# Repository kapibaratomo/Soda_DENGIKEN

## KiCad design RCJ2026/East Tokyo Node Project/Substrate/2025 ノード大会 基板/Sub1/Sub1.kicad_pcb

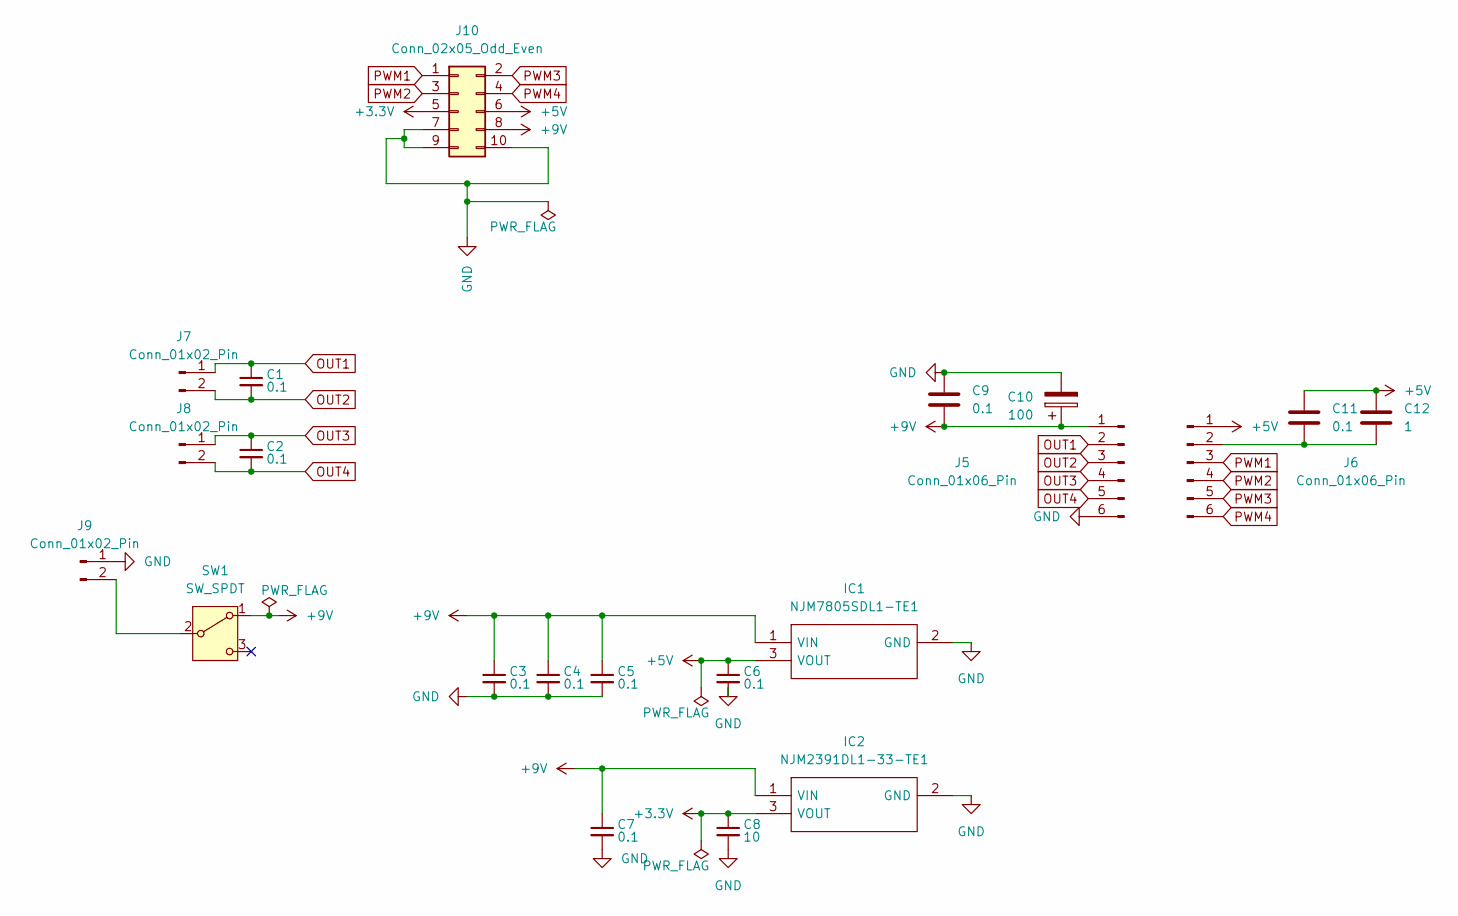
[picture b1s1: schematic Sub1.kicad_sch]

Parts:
C1, C2, C3, C4, C5, C6, C7, C9, C11: 0.1; C_0402_1005Metric
C8: 10; C_0603_1608Metric
C10: 100; C_Radial_D6.3mm_H7.0mm_P2.50mm
C12: 1; C_0402_1005Metric
IC1: NJM7805SDL1-TE1; NJM7805SDL1TE1
IC2: NJM2391DL1-33-TE1; NJM2391DL133TE1
J5, J6: Conn_01x06_Pin; PinSocket_1x06_P2.54mm_Vertical
J7, J8, J9: Conn_01x02_Pin; JST_XH_B2B-XH-A_1x02_P2.50mm_Vertical
J10: Conn_02x05_Odd_Even; IDC-Header_2x05_P2.54mm_Vertical
SW1: SW_SPDT; 2MS3T1B4M2QES

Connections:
+3.3V: C8.1, IC2.3 (VOUT), J10.5
+5V: C6.1, C11.1, C12.1, IC1.3 (VOUT), J6.1, J10.6
+9V: C3.1, C4.1, C5.1, C7.1, C9.2, C10.1, IC1.1 (VIN), IC2.1 (VIN), J5.1, J10.8, SW1.1 (A)
GND: C3.2, C4.2, C5.2, C6.2, C7.2, C8.2, C9.1, C10.2, IC1.2 (GND), IC2.2 (GND), J5.6, J9.1, J10.7, J10.9, J10.10
unnamed: C11.2, C12.2, J6.2
unnamed: J9.2, SW1.2 (B)
OUT1: C1.1, J5.2, J7.1
OUT2: C1.2, J5.3, J7.2
OUT3: C2.1, J5.4, J8.1
OUT4: C2.2, J5.5, J8.2
PWM1: J6.3, J10.1
PWM2: J6.4, J10.3
PWM3: J6.5, J10.2
PWM4: J6.6, J10.4

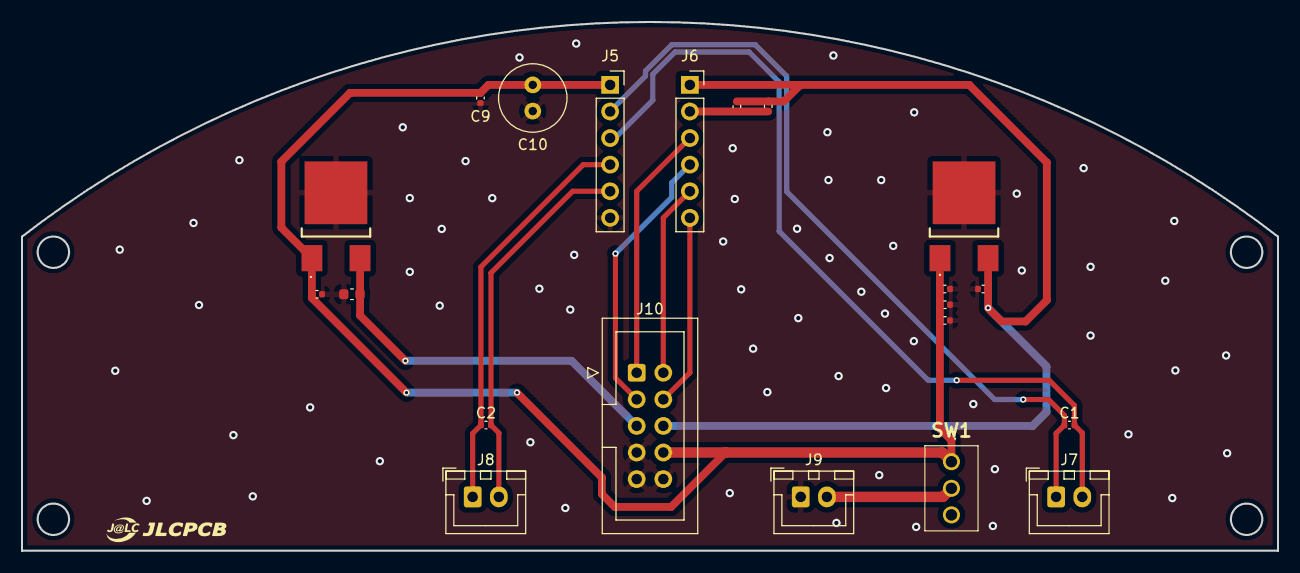
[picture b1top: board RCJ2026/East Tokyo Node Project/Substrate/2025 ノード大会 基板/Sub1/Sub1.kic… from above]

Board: 2 copper layers, 120.0 x 50.5 mm, 21 parts (0 on the bottom side), 14 nets.

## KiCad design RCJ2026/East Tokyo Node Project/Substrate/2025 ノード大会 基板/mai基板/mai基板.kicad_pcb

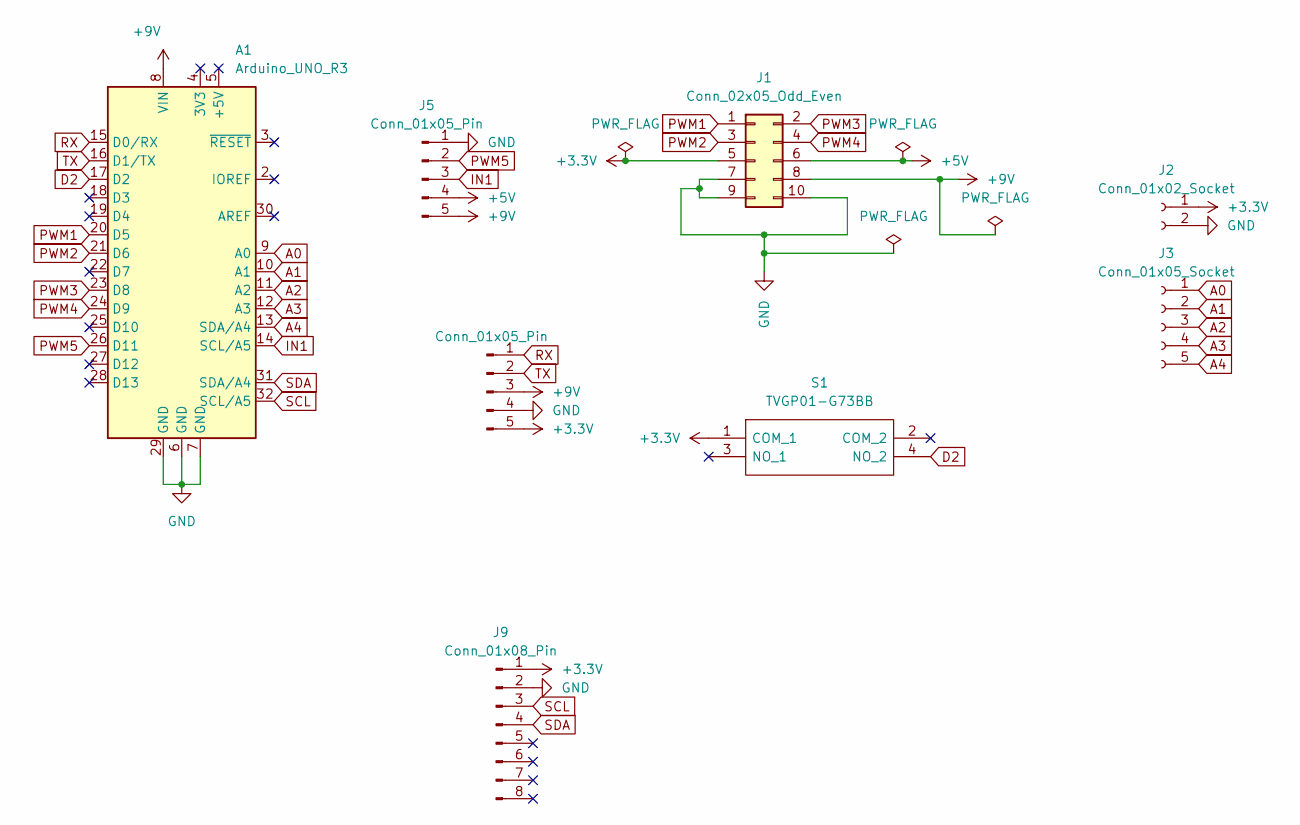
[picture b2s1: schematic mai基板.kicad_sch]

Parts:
A1: Arduino_UNO_R3
J1: Conn_02x05_Odd_Even; IDC-Header_2x05_P2.54mm_Vertical
J2: Conn_01x02_Socket; JST_XH_B2B-XH-A_1x02_P2.50mm_Vertical
J3: Conn_01x05_Socket; JST_XH_B5B-XH-A_1x05_P2.50mm_Vertical
J4, J5: Conn_01x05_Pin; JST_XH_B5B-XH-A_1x05_P2.50mm_Vertical
J9: Conn_01x08_Pin; PinSocket_1x08_P2.54mm_Vertical
S1: TVGP01-G73BB; TVGP01G73BB; Manufacturer_Part_Number TVGP01-G73BB

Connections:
+3.3V: J1.5, J2.1, J4.5, J9.1, S1.1 (COM_1)
+5V: J1.6, J5.4
+9V: A1.8 (VIN), J1.8, J4.3, J5.5
A0: A1.9 (A0), J3.1
A1: A1.10 (A1), J3.2
A2: A1.11 (A2), J3.3
A3: A1.12 (A3), J3.4
A4: A1.13 (SDA/A4), J3.5
D2: A1.17 (D2), S1.4 (NO_2)
GND: A1.6 (GND), A1.7 (GND), A1.29 (GND), J1.7, J1.9, J1.10, J2.2, J4.4, J5.1, J9.2
IN1: A1.14 (SCL/A5), J5.3
PWM1: A1.20 (D5), J1.1
PWM2: A1.21 (D6), J1.3
PWM3: A1.23 (D8), J1.2
PWM4: A1.24 (D9), J1.4
PWM5: A1.26 (D11), J5.2
RX: A1.15 (D0/RX), J4.1
SCL: A1.32 (SCL/A5), J9.3
SDA: A1.31 (SDA/A4), J9.4
TX: A1.16 (D1/TX), J4.2

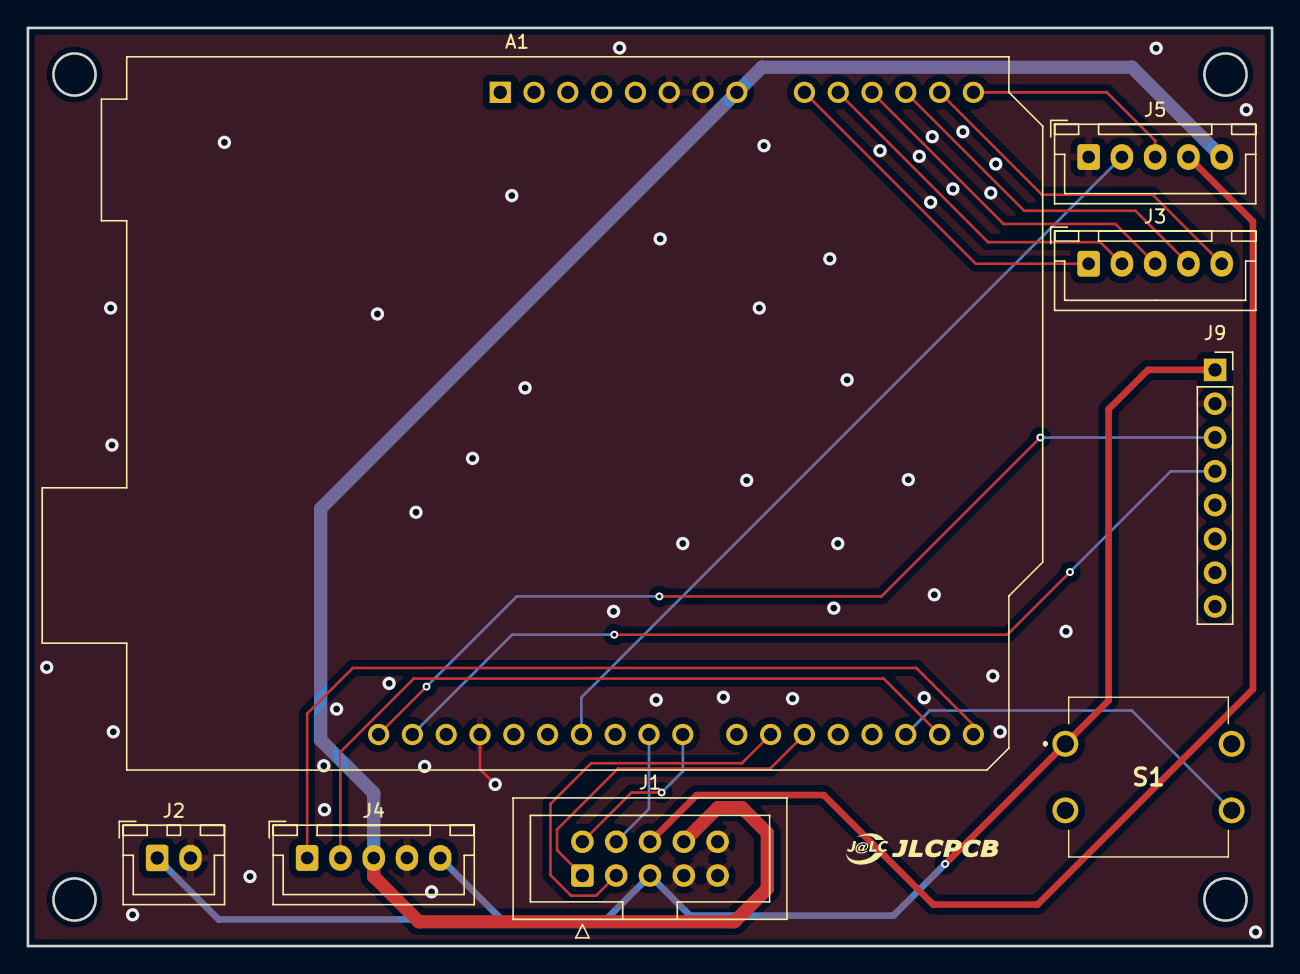
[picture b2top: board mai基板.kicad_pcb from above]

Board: 2 copper layers, 93.5 x 69.0 mm, 8 parts (0 on the bottom side), 20 nets.

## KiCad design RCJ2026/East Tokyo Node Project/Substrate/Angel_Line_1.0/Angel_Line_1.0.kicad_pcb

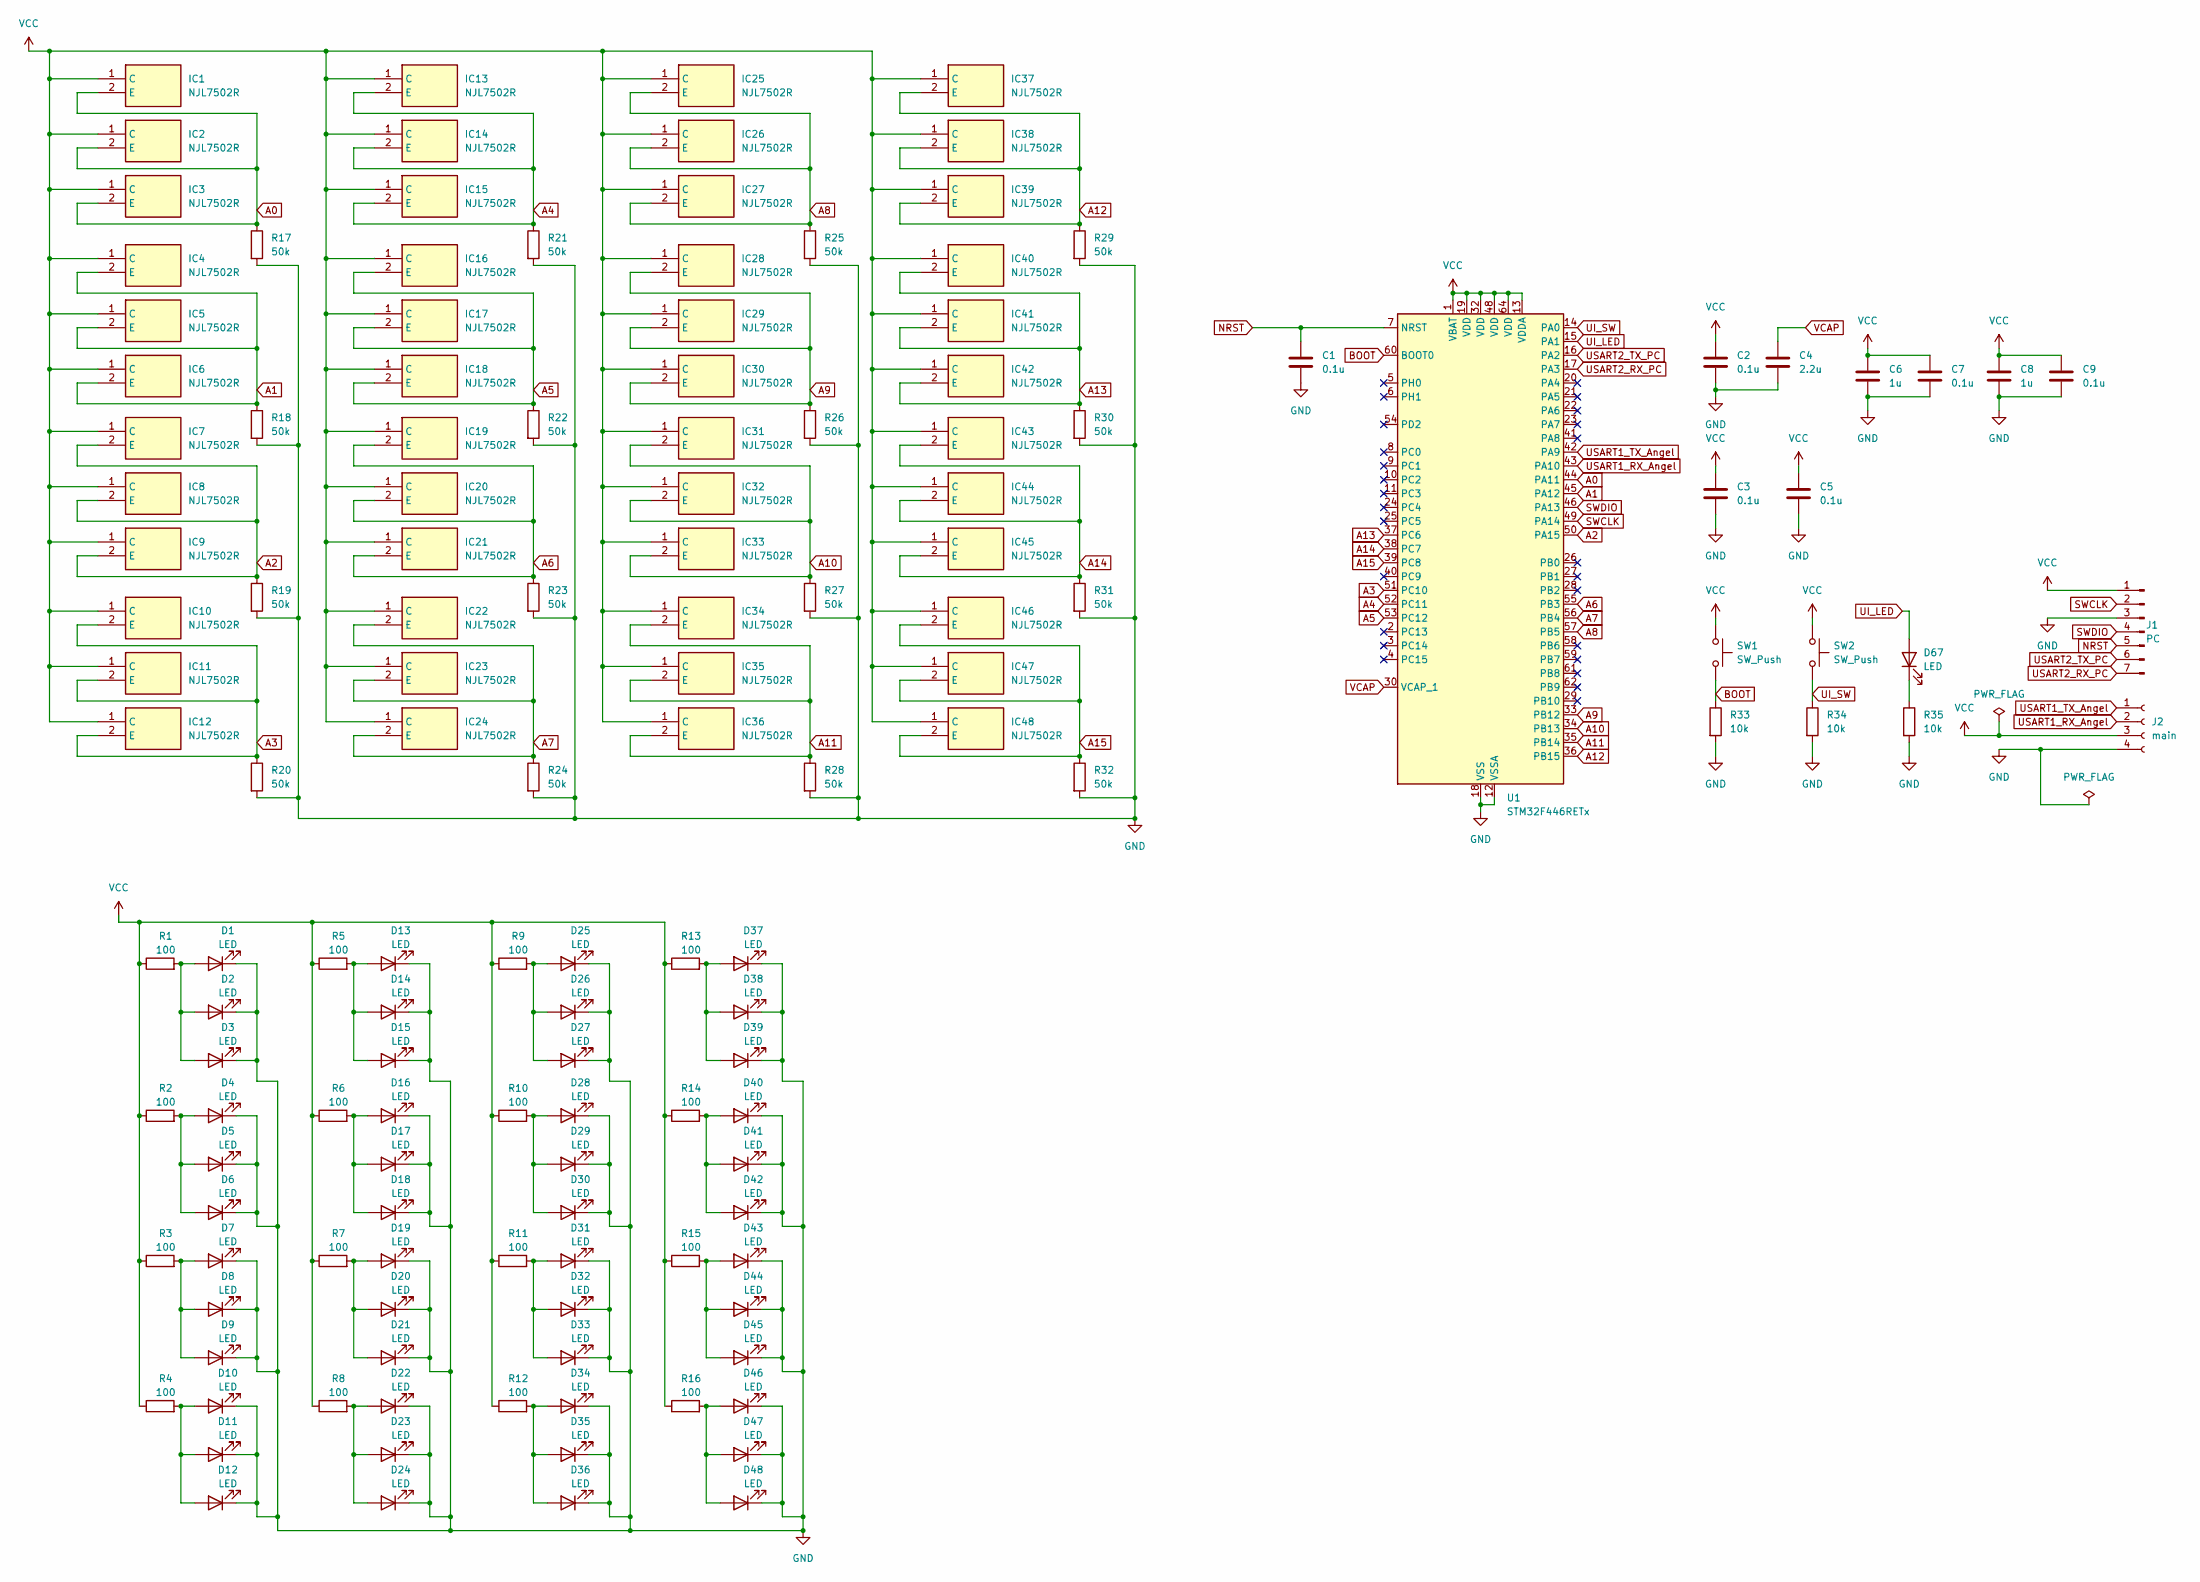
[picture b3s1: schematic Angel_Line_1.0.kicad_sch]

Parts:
C1, C2, C3, C5, C7, C9: 0.1u; C_0402_1005Metric
C4: 2.2u; C_0603_1608Metric
C6, C8: 1u; C_0402_1005Metric
D1, D2, D3, D4, D5, D6, D7, D8, D9, D10, D11, D12, D13, D14, D15, D16, D17, D18, D19, D20, D21, D22, D23, D24, D25, D26, D27, D28, D29, D30, D31, D32, D33, D34, D35, D36, D37, D38, D39, D40, D41, D42, D43, D44, D45, D46, D47, D48: LED; LED_0603_1608Metric_Pad1.05x0.95mm_HandSolder
D67: LED; LED_0603_1608Metric
IC1, IC2, IC3, IC4, IC5, IC6, IC7, IC8, IC9, IC10, IC11, IC12, IC13, IC14, IC15, IC16, IC17, IC18, IC19, IC20, IC21, IC22, IC23, IC24, IC25, IC26, IC27, IC28, IC29, IC30, IC31, IC32, IC33, IC34, IC35, IC36, IC37, IC38, IC39, IC40, IC41, IC42, IC43, IC44, IC45, IC46, IC47, IC48: NJL7502R; Manufacturer_Part_Number NJL7502R
J1: PC; PinHeader_1x07_P2.54mm_Vertical
J2: main; JST_XH_B4B-XH-A_1x04_P2.50mm_Vertical
R1, R2, R3, R4, R5, R6, R7, R8, R9, R10, R11, R12, R13, R14, R15, R16: 100; R_0603_1608Metric_Pad0.98x0.95mm_HandSolder
R17, R18, R19, R20, R21, R22, R23, R24, R25, R26, R27, R28, R29, R30, R31, R32: 50k; R_0603_1608Metric_Pad0.98x0.95mm_HandSolder
R33, R34, R35: 10k; R_0603_1608Metric
SW1, SW2: SW_Push; SKRPABE010
U1: STM32F446RETx; LQFP-64_10x10mm_P0.5mm

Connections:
A0: IC1.2 (E), IC2.2 (E), IC3.2 (E), R17.1, U1.44 (PA11)
A1: IC4.2 (E), IC5.2 (E), IC6.2 (E), R18.1, U1.45 (PA12)
A2: IC7.2 (E), IC8.2 (E), IC9.2 (E), R19.1, U1.50 (PA15)
A3: IC10.2 (E), IC11.2 (E), IC12.2 (E), R20.1, U1.51 (PC10)
A4: IC13.2 (E), IC14.2 (E), IC15.2 (E), R21.1, U1.52 (PC11)
A5: IC16.2 (E), IC17.2 (E), IC18.2 (E), R22.1, U1.53 (PC12)
A6: IC19.2 (E), IC20.2 (E), IC21.2 (E), R23.1, U1.55 (PB3)
A7: IC22.2 (E), IC23.2 (E), IC24.2 (E), R24.1, U1.56 (PB4)
A8: IC25.2 (E), IC26.2 (E), IC27.2 (E), R25.1, U1.57 (PB5)
A9: IC28.2 (E), IC29.2 (E), IC30.2 (E), R26.1, U1.33 (PB12)
A10: IC31.2 (E), IC32.2 (E), IC33.2 (E), R27.1, U1.34 (PB13)
A11: IC34.2 (E), IC35.2 (E), IC36.2 (E), R28.1, U1.35 (PB14)
A12: IC37.2 (E), IC38.2 (E), IC39.2 (E), R29.1, U1.36 (PB15)
A13: IC40.2 (E), IC41.2 (E), IC42.2 (E), R30.1, U1.37 (PC6)
A14: IC43.2 (E), IC44.2 (E), IC45.2 (E), R31.1, U1.38 (PC7)
A15: IC46.2 (E), IC47.2 (E), IC48.2 (E), R32.1, U1.39 (PC8)
BOOT: R33.1, SW1.2, U1.60 (BOOT0)
GND: C1.2, C2.2, C3.2, C4.2, C5.2, C6.2, C7.2, C8.2, C9.2, D1.1 (K), D2.1 (K), D3.1 (K), D4.1 (K), D5.1 (K), D6.1 (K), D7.1 (K), D8.1 (K), D9.1 (K), D10.1 (K), D11.1 (K), D12.1 (K), D13.1 (K), D14.1 (K), D15.1 (K), D16.1 (K), D17.1 (K), D18.1 (K), D19.1 (K), D20.1 (K), D21.1 (K), D22.1 (K), D23.1 (K), D24.1 (K), D25.1 (K), D26.1 (K), D27.1 (K), D28.1 (K), D29.1 (K), D30.1 (K), D31.1 (K), D32.1 (K), D33.1 (K), D34.1 (K), D35.1 (K), D36.1 (K), D37.1 (K), D38.1 (K), D39.1 (K), D40.1 (K), D41.1 (K), D42.1 (K), D43.1 (K), D44.1 (K), D45.1 (K), D46.1 (K), D47.1 (K), D48.1 (K), J1.3, J2.4, R17.2, R18.2, R19.2, R20.2, R21.2, R22.2, R23.2, R24.2, R25.2, R26.2, R27.2, R28.2, R29.2, R30.2, R31.2, R32.2, R33.2, R34.2, R35.2, U1.12 (VSSA), U1.18 (VSS), U1.31 (VSS), U1.47 (VSS), U1.63 (VSS)
NRST: C1.1, J1.5, U1.7 (NRST)
unnamed: D1.2 (A), D2.2 (A), D3.2 (A), R1.2
unnamed: D4.2 (A), D5.2 (A), D6.2 (A), R2.2
unnamed: D7.2 (A), D8.2 (A), D9.2 (A), R3.2
unnamed: D10.2 (A), D11.2 (A), D12.2 (A), R4.2
unnamed: D13.2 (A), D14.2 (A), D15.2 (A), R5.2
unnamed: D16.2 (A), D17.2 (A), D18.2 (A), R6.2
unnamed: D19.2 (A), D20.2 (A), D21.2 (A), R7.2
unnamed: D22.2 (A), D23.2 (A), D24.2 (A), R8.2
unnamed: D25.2 (A), D26.2 (A), D27.2 (A), R9.2
unnamed: D28.2 (A), D29.2 (A), D30.2 (A), R10.2
unnamed: D31.2 (A), D32.2 (A), D33.2 (A), R11.2
unnamed: D34.2 (A), D35.2 (A), D36.2 (A), R12.2
unnamed: D37.2 (A), D38.2 (A), D39.2 (A), R13.2
unnamed: D40.2 (A), D41.2 (A), D42.2 (A), R14.2
unnamed: D43.2 (A), D44.2 (A), D45.2 (A), R15.2
unnamed: D46.2 (A), D47.2 (A), D48.2 (A), R16.2
unnamed: D67.1 (K), R35.1
SWCLK: J1.2, U1.49 (PA14)
SWDIO: J1.4, U1.46 (PA13)
UI_LED: D67.2 (A), U1.15 (PA1)
UI_SW: R34.1, SW2.2, U1.14 (PA0)
USART1_RX_Angel: J2.2, U1.43 (PA10)
USART1_TX_Angel: J2.1, U1.42 (PA9)
USART2_RX_PC: J1.7, U1.17 (PA3)
USART2_TX_PC: J1.6, U1.16 (PA2)
VCAP: C4.1, U1.30 (VCAP_1)
VCC: C2.1, C3.1, C5.1, C6.1, C7.1, C8.1, C9.1, IC1.1 (C), IC2.1 (C), IC3.1 (C), IC4.1 (C), IC5.1 (C), IC6.1 (C), IC7.1 (C), IC8.1 (C), IC9.1 (C), IC10.1 (C), IC11.1 (C), IC12.1 (C), IC13.1 (C), IC14.1 (C), IC15.1 (C), IC16.1 (C), IC17.1 (C), IC18.1 (C), IC19.1 (C), IC20.1 (C), IC21.1 (C), IC22.1 (C), IC23.1 (C), IC24.1 (C), IC25.1 (C), IC26.1 (C), IC27.1 (C), IC28.1 (C), IC29.1 (C), IC30.1 (C), IC31.1 (C), IC32.1 (C), IC33.1 (C), IC34.1 (C), IC35.1 (C), IC36.1 (C), IC37.1 (C), IC38.1 (C), IC39.1 (C), IC40.1 (C), IC41.1 (C), IC42.1 (C), IC43.1 (C), IC44.1 (C), IC45.1 (C), IC46.1 (C), IC47.1 (C), IC48.1 (C), J1.1, J2.3, R1.1, R2.1, R3.1, R4.1, R5.1, R6.1, R7.1, R8.1, R9.1, R10.1, R11.1, R12.1, R13.1, R14.1, R15.1, R16.1, SW1.1, SW2.1, U1.1 (VBAT), U1.13 (VDDA), U1.19 (VDD), U1.32 (VDD), U1.48 (VDD), U1.64 (VDD)

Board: 2 copper layers, 146 parts (48 on the bottom side), 46 nets, no tracks yet.

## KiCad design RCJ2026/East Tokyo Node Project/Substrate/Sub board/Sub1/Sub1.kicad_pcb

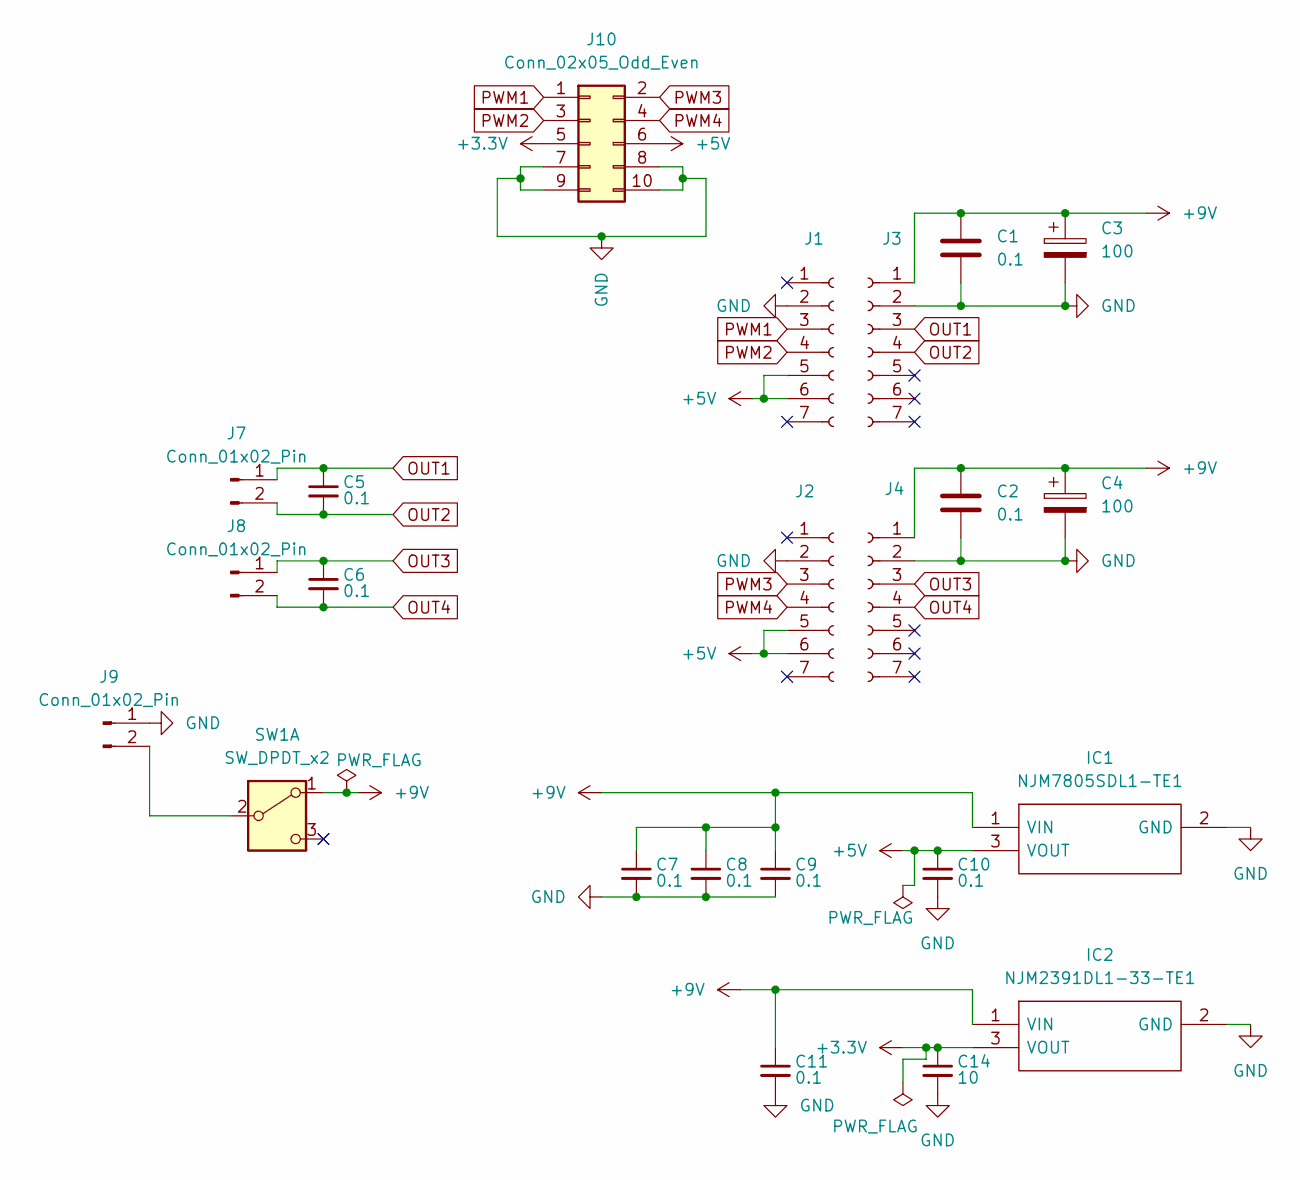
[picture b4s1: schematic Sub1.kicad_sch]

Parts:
C1, C2, C5, C6, C7, C8, C9, C10, C11: 0.1; C_0402_1005Metric
C3, C4: 100; OS-CON 100μF16V105℃
C14: 10; C_0402_1005Metric
IC1: NJM7805SDL1-TE1; NJM7805SDL1TE1
IC2: NJM2391DL1-33-TE1; NJM2391DL133TE1
J1, J2, J3, J4: Conn_01x07_Socket; PinSocket_1x07_P2.54mm_Vertical
J7, J8, J9: Conn_01x02_Pin; JST_XH_B2B-XH-A_1x02_P2.50mm_Vertical
J10: Conn_02x05_Odd_Even; IDC-Header_2x05_P2.54mm_Vertical
SW1: SW_DPDT_x2; 2MS3T1B4M2QES

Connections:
+3.3V: C14.1, IC2.3 (VOUT), J10.5
+5V: C10.1, IC1.3 (VOUT), J1.5, J1.6, J2.5, J2.6, J10.6
+9V: C1.1, C2.1, C3.1, C4.1, C7.1, C8.1, C9.1, C11.1, IC1.1 (VIN), IC2.1 (VIN), J3.1, J4.1, SW1.1 (A)
GND: C1.2, C2.2, C3.2, C4.2, C7.2, C8.2, C9.2, C10.2, C11.2, C14.2, IC1.2 (GND), IC2.2 (GND), J1.2, J2.2, J3.2, J4.2, J9.1, J10.7, J10.8, J10.9, J10.10
unnamed: J9.2, SW1.2 (B)
OUT1: C5.1, J3.3, J7.1
OUT2: C5.2, J3.4, J7.2
OUT3: C6.1, J4.3, J8.1
OUT4: C6.2, J4.4, J8.2
PWM1: J1.3, J10.1
PWM2: J1.4, J10.3
PWM3: J2.3, J10.2
PWM4: J2.4, J10.4

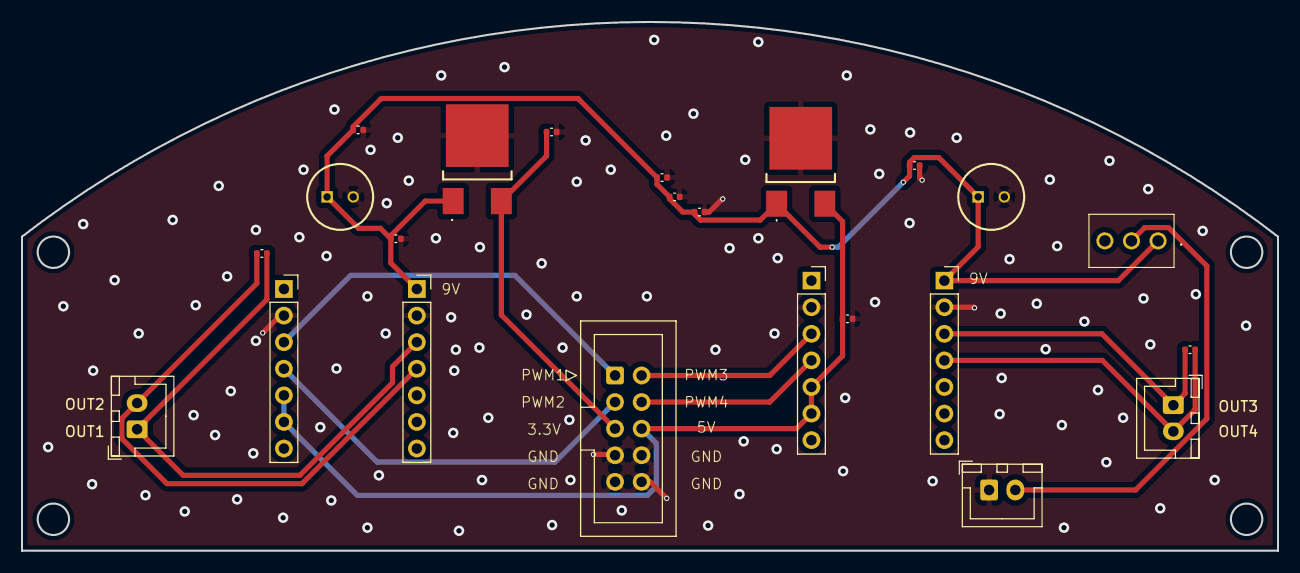
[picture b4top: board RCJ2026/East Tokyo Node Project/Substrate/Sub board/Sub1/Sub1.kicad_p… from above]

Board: 2 copper layers, 120.0 x 50.5 mm, 23 parts (0 on the bottom side), 13 nets.

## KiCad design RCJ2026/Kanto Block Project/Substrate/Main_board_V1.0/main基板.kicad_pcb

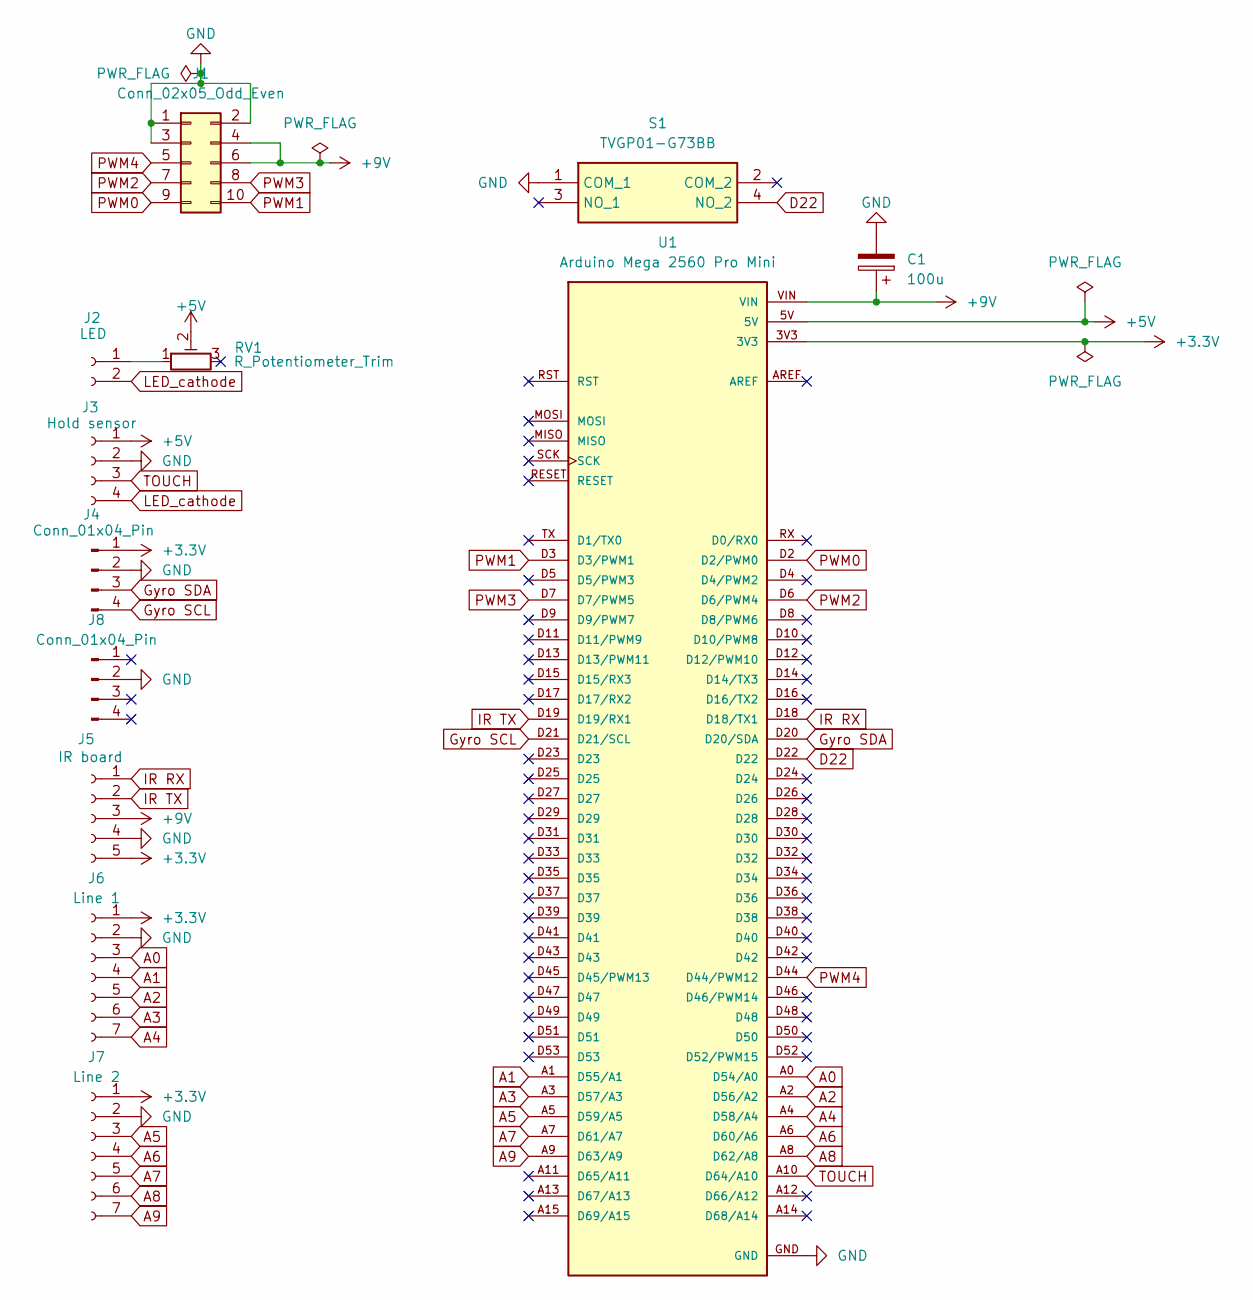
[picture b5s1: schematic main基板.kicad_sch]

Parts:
C1: 100u; C_Radial_D6.3mm_H7.0mm_P2.50mm
J1: Conn_02x05_Odd_Even; IDC-Header_2x05_P2.54mm_Vertical
J2: LED; JST_XH_B2B-XH-A_1x02_P2.50mm_Vertical
J3: Hold sensor; JST_XH_B4B-XH-A_1x04_P2.50mm_Vertical
J4, J8: Conn_01x04_Pin; PinSocket_1x04_P2.54mm_Vertical
J5: IR board; JST_XH_B5B-XH-A_1x05_P2.50mm_Vertical
J6: Line 1; JST_XH_B7B-XH-A_1x07_P2.50mm_Vertical
J7: Line 2; JST_XH_B7B-XH-A_1x07_P2.50mm_Vertical
RV1: R_Potentiometer_Trim; Potentiometer_Vishay_T73YP_Vertical
S1: TVGP01-G73BB; TVGP01G73BB; Manufacturer_Part_Number TVGP01-G73BB
U1: Arduino Mega 2560 Pro Mini; MODULE_MEGA_PRO_EMBED_CH340G___ATMEGA2560; PARTREV 12/May/2017

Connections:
+3.3V: J4.1, J5.5, J6.1, J7.1, U1.3V3
+5V: J3.1, RV1.2, U1.5V
+9V: C1.1, J1.4, J1.6, J5.3, U1.VIN
A0: J6.3, U1.A0 (D54/A0)
A1: J6.4, U1.A1 (D55/A1)
A2: J6.5, U1.A2 (D56/A2)
A3: J6.6, U1.A3 (D57/A3)
A4: J6.7, U1.A4 (D58/A4)
A5: J7.3, U1.A5 (D59/A5)
A6: J7.4, U1.A6 (D60/A6)
A7: J7.5, U1.A7 (D61/A7)
A8: J7.6, U1.A8 (D62/A8)
A9: J7.7, U1.A9 (D63/A9)
D22: S1.4 (NO_2), U1.D22
GND: C1.2, J1.1, J1.2, J1.3, J3.2, J4.2, J5.4, J6.2, J7.2, J8.2, S1.1 (COM_1), U1.GND
Gyro SCL: J4.4, U1.D21 (D21/SCL)
Gyro SDA: J4.3, U1.D20 (D20/SDA)
IR RX: J5.1, U1.D18 (D18/TX1)
IR TX: J5.2, U1.D19 (D19/RX1)
LED_cathode: J2.2, J3.4
unnamed: J2.1, RV1.1
PWM0: J1.9, U1.D2 (D2/PWM0)
PWM1: J1.10, U1.D3 (D3/PWM1)
PWM2: J1.7, U1.D6 (D6/PWM4)
PWM3: J1.8, U1.D7 (D7/PWM5)
PWM4: J1.5, U1.D44 (D44/PWM12)
TOUCH: J3.3, U1.A10 (D64/A10)

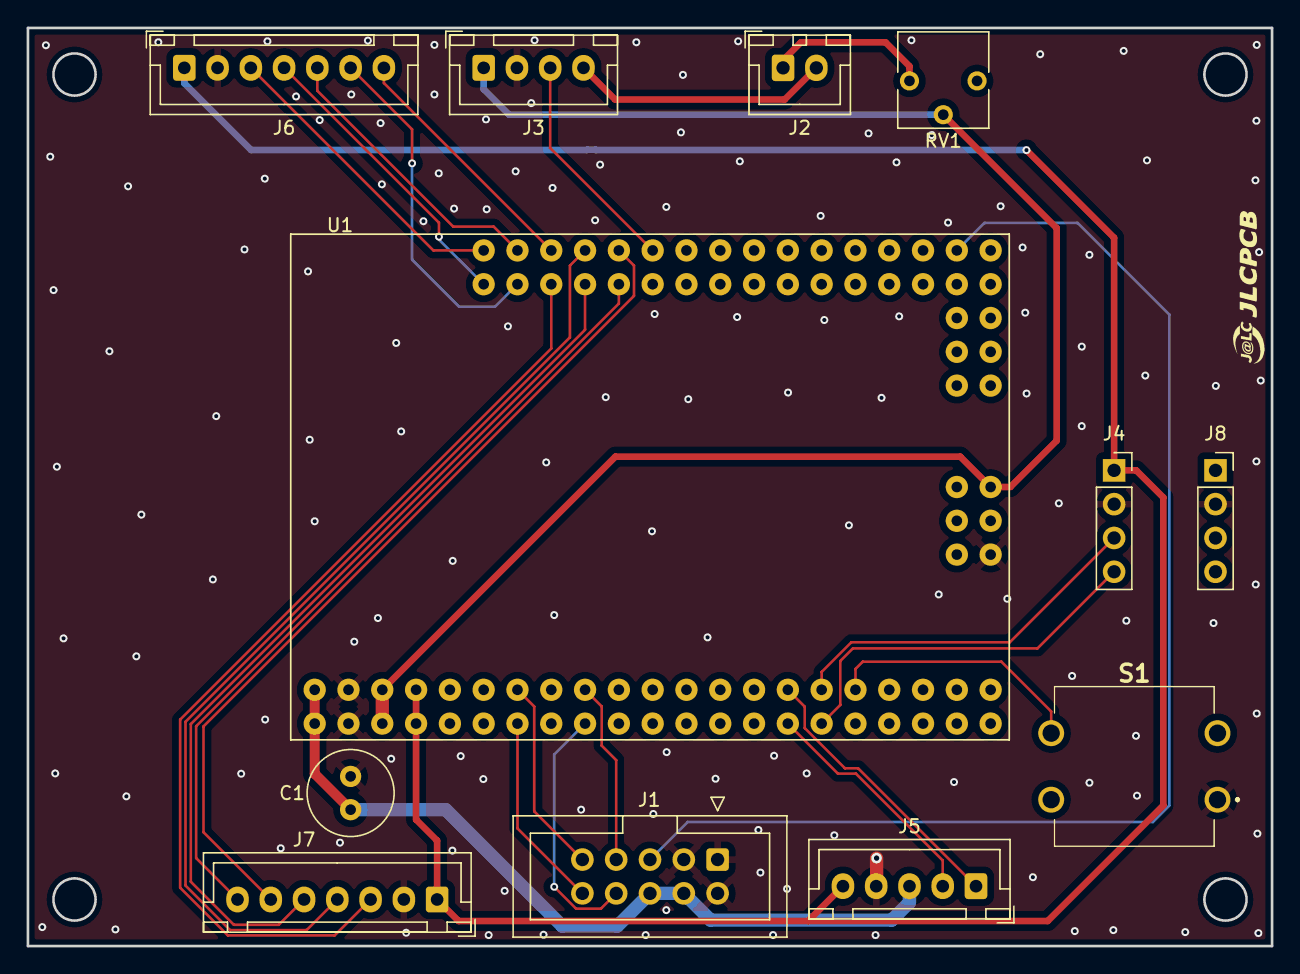
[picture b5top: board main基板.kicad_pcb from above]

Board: 2 copper layers, 93.5 x 69.0 mm, 12 parts (0 on the bottom side), 27 nets.
